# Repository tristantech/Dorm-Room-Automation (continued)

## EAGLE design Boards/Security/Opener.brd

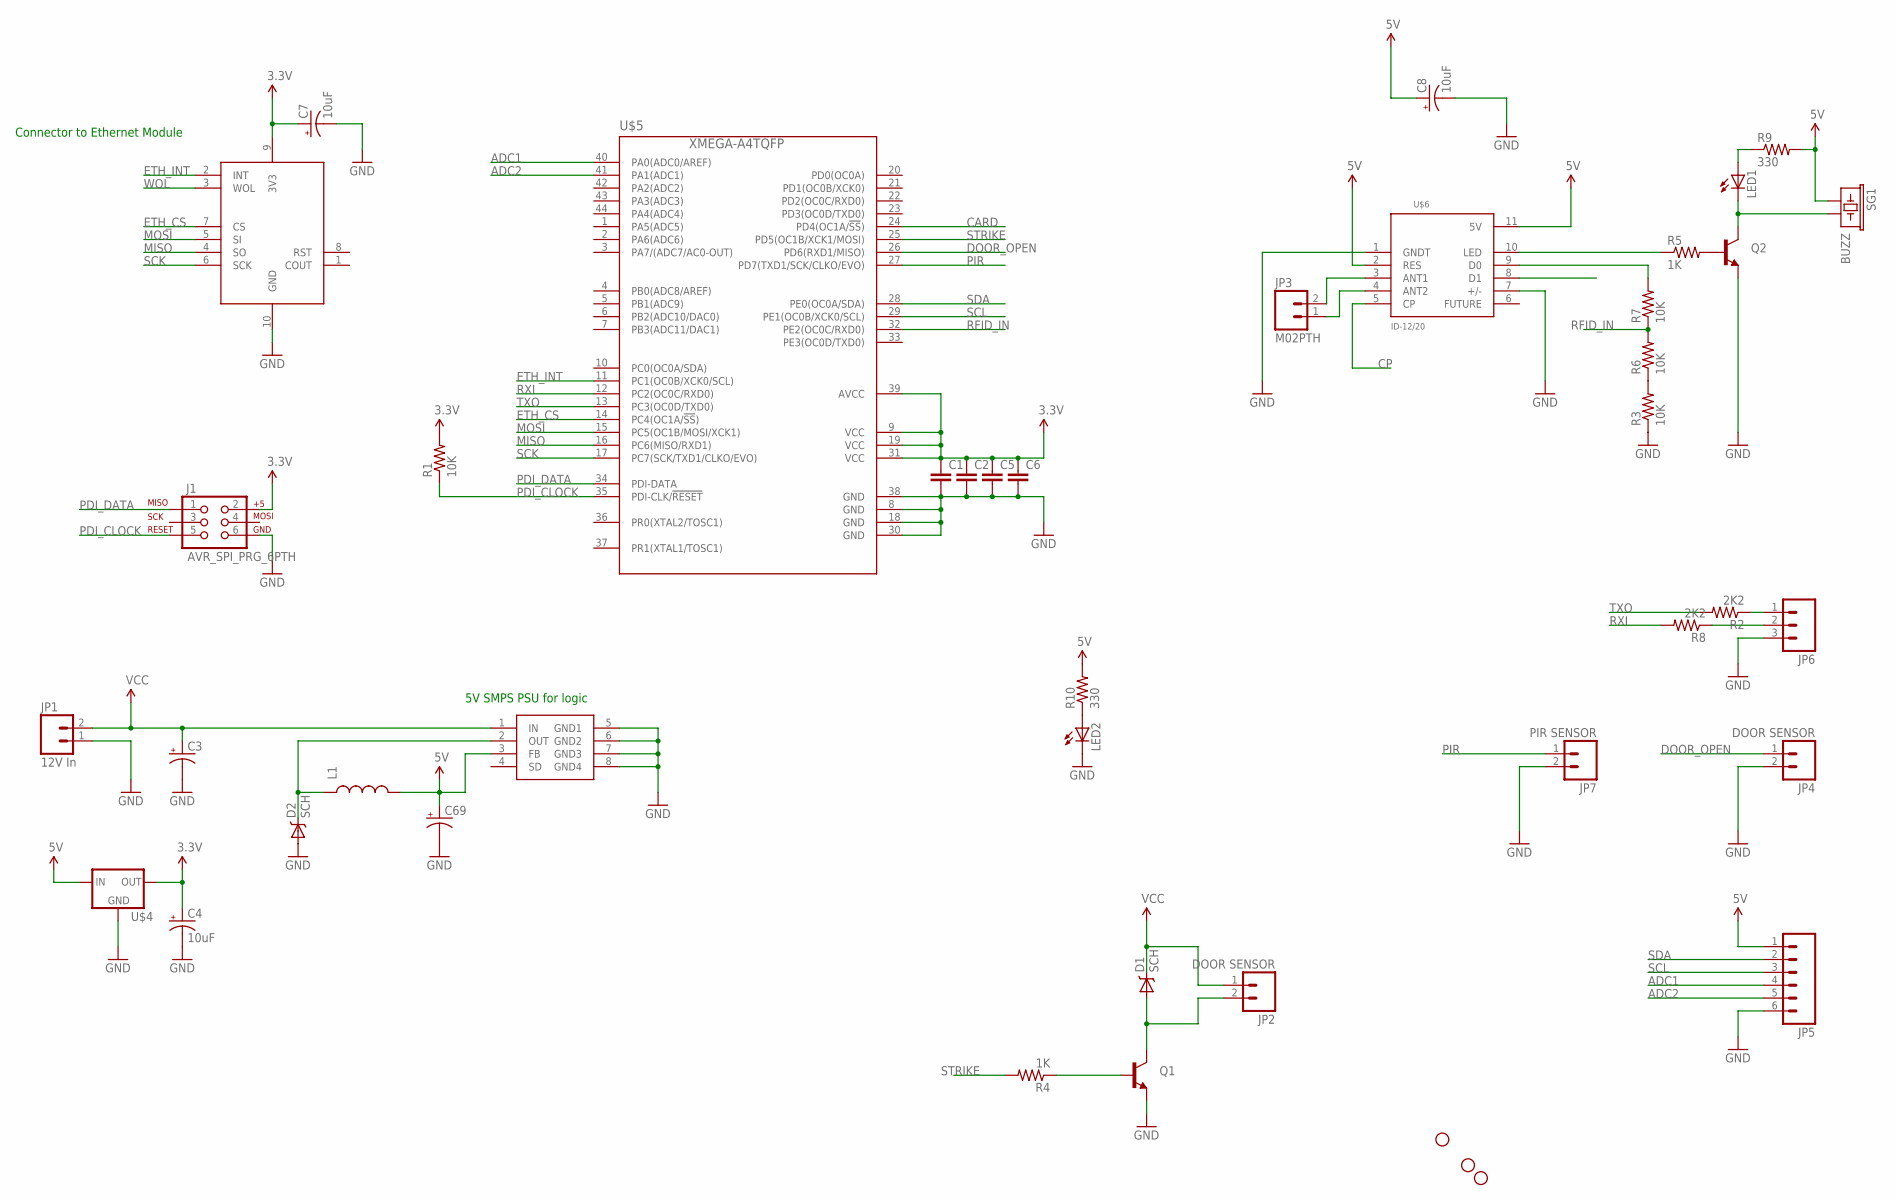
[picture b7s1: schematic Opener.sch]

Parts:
C1, C2, C5, C6: CAP0603-CAP; 0603-CAP
C3, C69: CAP_POLPTH1; CPOL-RADIAL-100UF-25V
C4, C7, C8: 10uF; EIA3216
D1, D2: SCH; SMA-DIODE
J1: AVR_SPI_PRG_6PTH; 2X3
JP1: 12V In; SCREWTERMINAL-3.5MM-2
JP2, JP4: DOOR SENSOR; MOLEX-1X2
JP3: M02PTH; 1X02
JP5: M06SIP; 1X06
JP6: M03PTH; 1X03
JP7: PIR SENSOR; MOLEX-1X2
L1: INDUCTOR1206H*; INDUCTOR-1206
LED1, LED2: LED-FKIT-1206; FKIT-LED-1206
Q1: TRANSISTOR_NPNTO92; TO-92
Q2: TRANSISTOR_NPNSOT23; SOT23
R1, R3, R6, R7: 10K; 1206
R2, R8: 2K2; 1206
R4, R5: 1K; 1206
R9, R10: 330; 1206
SG1: BUZZ; BUZZER-CCV
STANDOFF1, STANDOFF3, STANDOFF4: STAND-OFF
U$1: ETHMODULE; 2X5
U$3: AP1509-33; SOIC-8
U$4: V_REG_MIC2920; SOT223
U$5: XMEGA-A4TQFP; TQFP44
U$6: ID-12/20; ID-12

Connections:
3.3V: C1.1, C2.1, C4.A (+), C5.1, C6.1, C7.A (+), J1.2, R1.2, U$1.9 (3V3), U$4.3 (OUT), U$5.9 (VCC), U$5.19 (VCC), U$5.31 (VCC), U$5.39 (AVCC)
5V: C8.A (+), C69.1 (+), JP5.1, L1.P$2 (2), R9.2, R10.2, SG1.+ (1), U$3.3 (FB), U$4.1 (IN), U$6.2 (RES), U$6.11 (5V)
ADC1: JP5.4, U$5.40 (PA0(ADC0/AREF))
ADC2: JP5.5, U$5.41 (PA1(ADC1))
CARD: U$5.24 (PD4(OC1A/!SS!))
COUT: U$1.1 (COUT)
CP: U$6.5 (CP)
DOOR_OPEN: JP4.1, U$5.26 (PD6(RXD1/MISO))
ETH_CS: U$1.7 (CS), U$5.14 (PC4(OC1A/!SS!))
ETH_INT: U$1.2 (INT), U$5.11 (PC1(OC0B/XCK0/SCL))
GND: C1.2, C2.2, C3.2 (-), C4.C (-), C5.2, C6.2, C7.C (-), C8.C (-), C69.2 (-), D2.A, J1.6, JP1.1, JP4.2, JP5.6, JP6.3, JP7.2, LED2.C, Q1.1 (E), Q2.2 (E), R3.1, U$1.10 (GND), U$3.5 (GND1), U$3.6 (GND2), U$3.7 (GND3), U$3.8 (GND4), U$4.2 (GND), U$5.8 (GND), U$5.18 (GND), U$5.30 (GND), U$5.38 (GND), U$6.1 (GNDT), U$6.7 (+/-)
MISO: U$1.4 (SO), U$5.16 (PC6(MISO/RXD1))
MOSI: U$1.5 (SI), U$5.15 (PC5(OC1B/MOSI/XCK1))
unnamed: Q1.2 (B), R4.1
unnamed: JP3.2, U$6.3 (ANT1)
unnamed: D2.C, L1.P$1 (1), U$3.2 (OUT)
unnamed: R7.2, U$6.9 (D0)
unnamed: R3.2, R6.1
unnamed: JP3.1, U$6.4 (ANT2)
unnamed: D1.A, JP2.2, Q1.3 (C)
unnamed: R5.1, U$6.10 (LED)
unnamed: Q2.1 (B), R5.2
unnamed: LED1.C, Q2.3 (C), SG1.- (2)
unnamed: LED1.A, R9.1
unnamed: JP6.1, R2.1
unnamed: LED2.A, R10.1
unnamed: JP6.2, R8.1
PDI_CLOCK: J1.5, R1.1, U$5.35 (PDI-CLK/!RESET)
PDI_DATA: J1.1, U$5.34 (PDI-DATA)
PIR: JP7.1, U$5.27 (PD7(TXD1/SCK/CLKO/EVO))
RFID_IN: R6.2, R7.1, U$5.32 (PE2(OC0C/RXD0))
RST: U$1.8 (RST)
RXI: R8.2, U$5.12 (PC2(OC0C/RXD0))
SCK: U$1.6 (SCK), U$5.17 (PC7(SCK/TXD1/CLKO/EVO))
SCL: JP5.3, U$5.29 (PE1(OC0B/XCK0/SCL))
SDA: JP5.2, U$5.28 (PE0(OC0A/SDA))
STRIKE: R4.2, U$5.25 (PD5(OC1B/XCK1/MOSI))
TXO: R2.2, U$5.13 (PC3(OC0D/TXD0))
VCC: C3.1 (+), D1.C, JP1.2, JP2.1, U$3.1 (IN)
WOL: U$1.3 (WOL)

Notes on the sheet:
Connector to Ethernet Module
5V SMPS PSU for logic

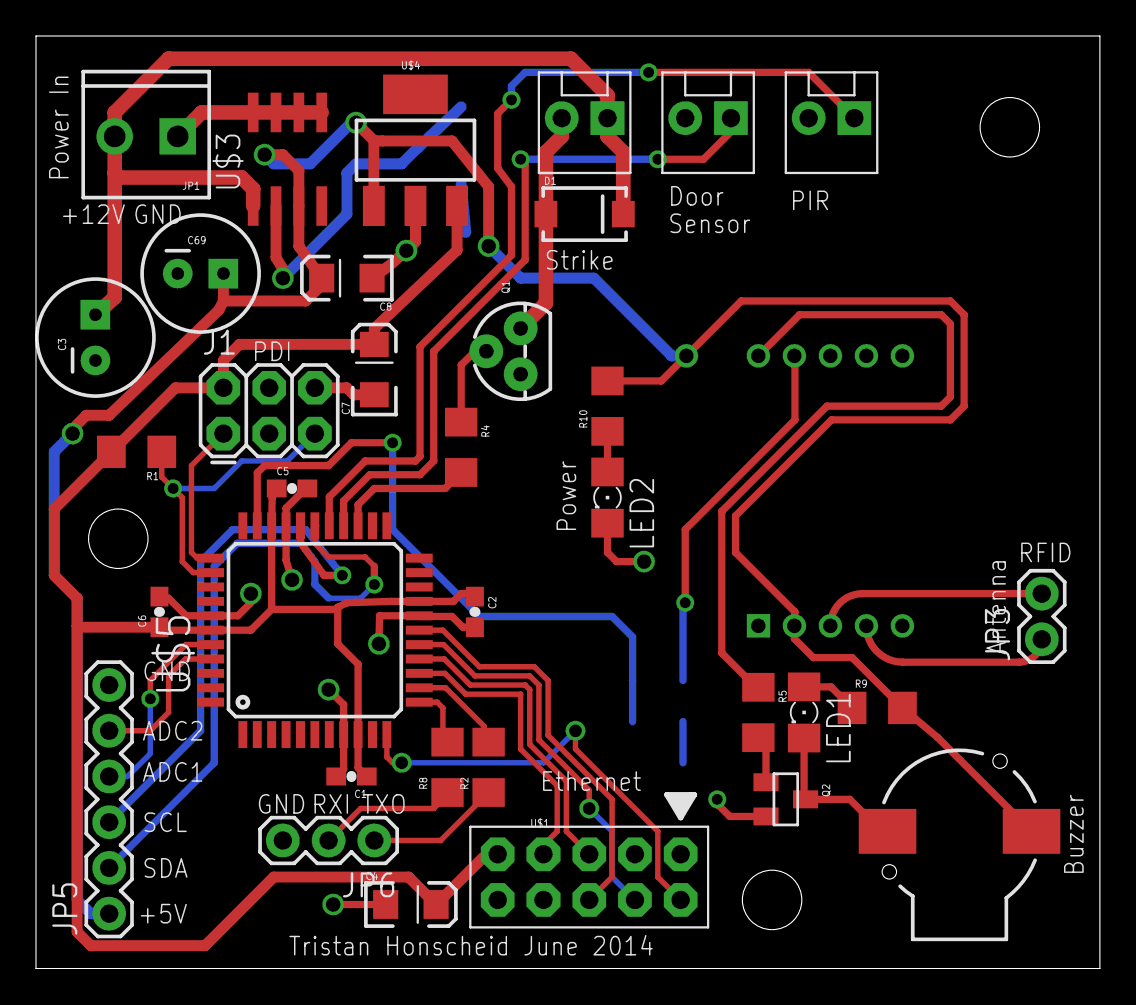
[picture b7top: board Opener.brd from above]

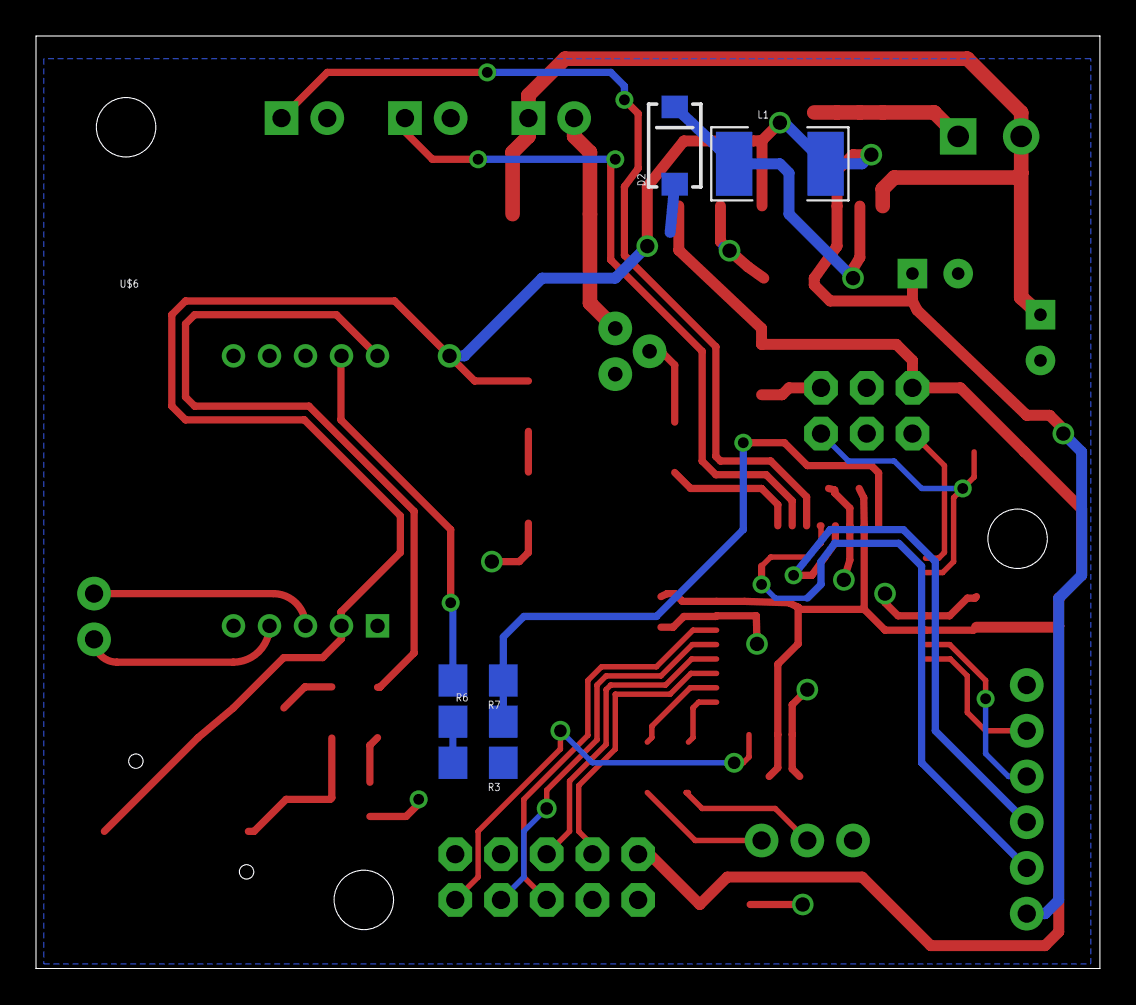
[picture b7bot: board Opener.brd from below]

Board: 2 copper layers, 59.1 x 51.8 mm, 43 parts (6 on the bottom side), 35 nets.

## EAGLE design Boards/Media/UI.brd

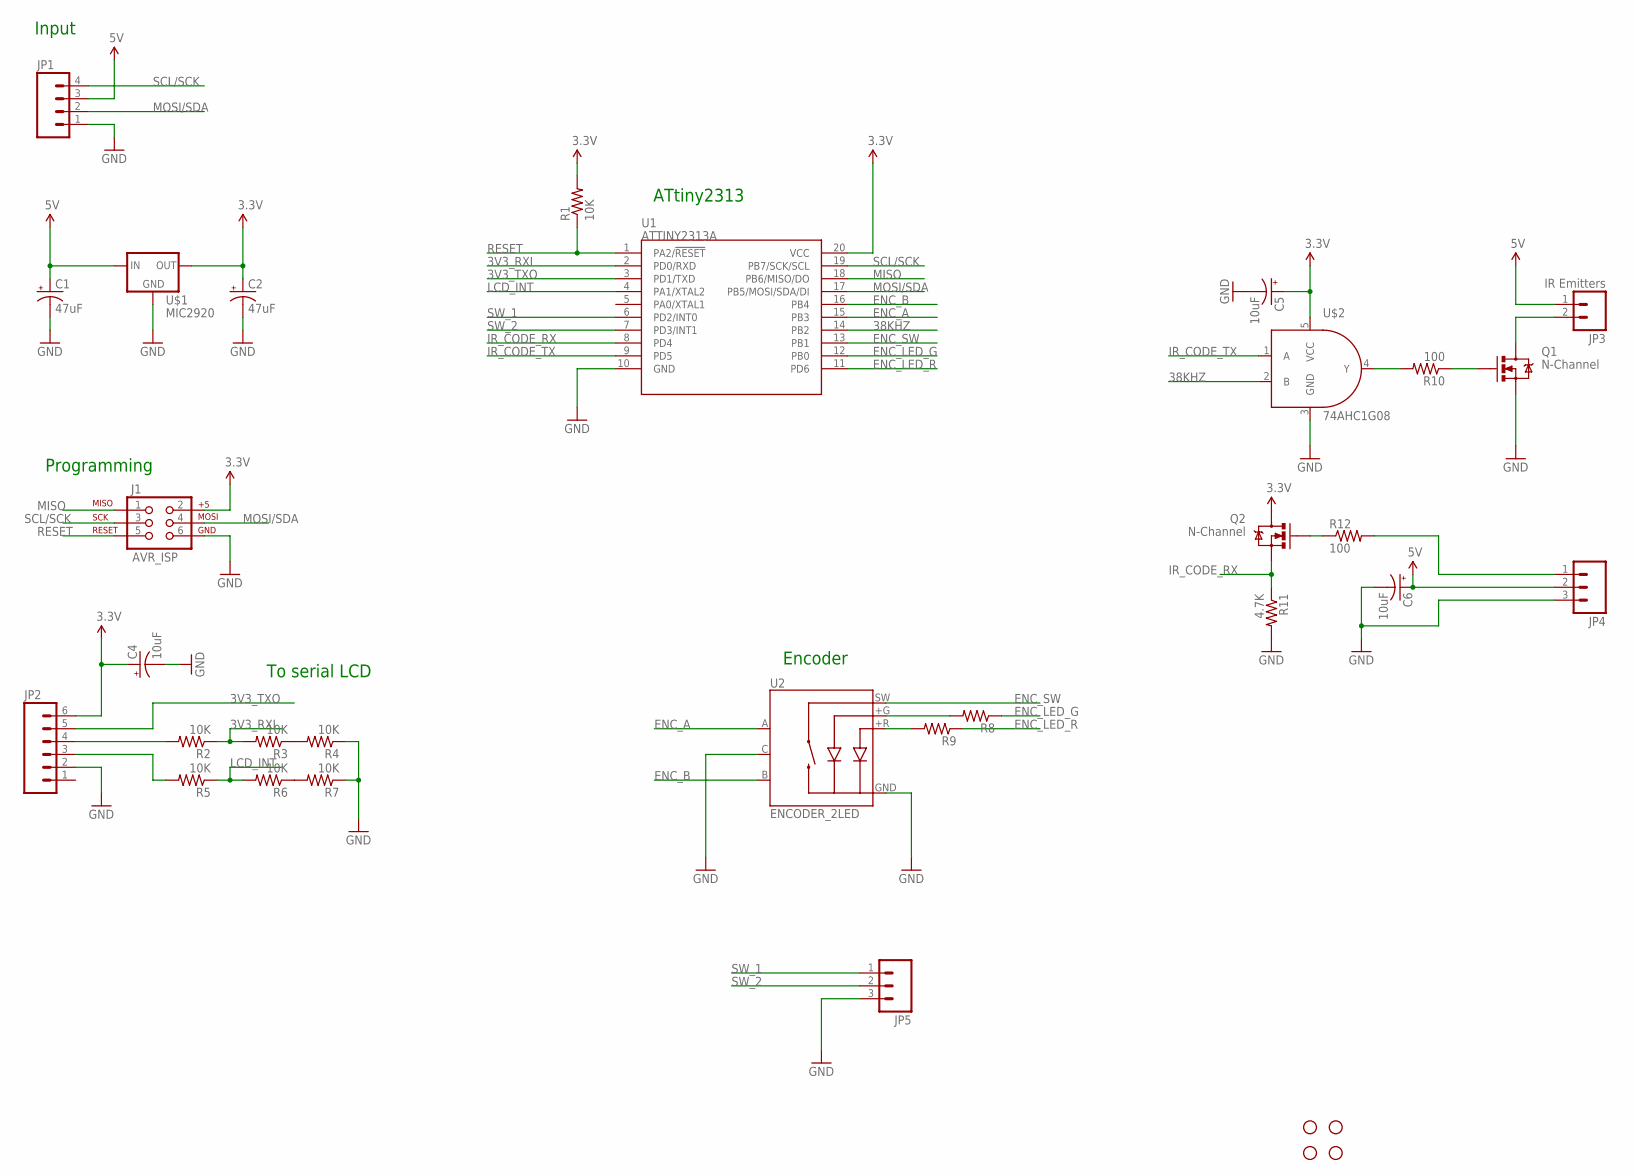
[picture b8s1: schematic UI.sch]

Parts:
C1, C2: 47uF; CPOL-RADIAL-10UF-25V
C4, C5, C6: 10uF; EIA3216
J1: AVR_ISP; 2X3
JP1: M04POLAR; MOLEX-1X4
JP2: M06POLAR; MOLEX-1X6
JP3: IR Emitters; SCREWTERMINAL-3.5MM-2
JP4, JP5: M03PTH; 1X03
Q1, Q2: N-Channel; SOT23
R1, R2, R3, R4, R5, R6, R7: 10K; 1206
R8, R9: RESISTOR1206; 1206
R10, R12: 100; 1206
R11: 4.7K; 1206
STANDOFF1, STANDOFF2, STANDOFF3, STANDOFF4: STAND-OFF
U1: ATTINY2313A; SOP20W
U2: ENCODER_2LED; ENCODER_LED_2
U$1: MIC2920; SOT223
U$2: 74AHC1G08; SOT23-5

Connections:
3.3V: C2.1 (+), C4.A (+), C5.A (+), J1.2, JP2.6, Q2.3 (D), R1.2, U1.20 (VCC), U$1.3 (OUT), U$2.5 (VCC)
3V3_RXI: R2.1, R3.2, U1.2 (PD0/RXD)
3V3_TXO: JP2.5, U1.3 (PD1/TXD)
5V: C1.1 (+), C6.A (+), JP1.3, JP3.1, JP4.2, U$1.1 (IN)
38KHZ: U1.14 (PB2), U$2.2 (B)
ENC_A: U1.15 (PB3), U2.A
ENC_B: U1.16 (PB4), U2.B
ENC_LED_G: R8.1, U1.12 (PB0)
ENC_LED_R: R9.1, U1.11 (PD6)
ENC_SW: U1.13 (PB1), U2.SW
GND: C1.2 (-), C2.2 (-), C4.C (-), C5.C (-), C6.C (-), J1.6, JP1.1, JP2.2, JP4.3, JP5.3, Q1.2 (S), R4.1, R7.1, R11.2, U1.10 (GND), U2.C, U2.GND (-), U$1.2 (GND), U$2.3 (GND)
IR_CODE_RX: Q2.2 (S), R11.1, U1.8 (PD4)
IR_CODE_TX: U1.9 (PD5), U$2.1 (A)
LCD_INT: R5.1, R6.2, U1.4 (PA1/XTAL2)
MISO: J1.1, U1.18 (PB6/MISO/DO)
MOSI/SDA: J1.4, JP1.2, U1.17 (PB5/MOSI/SDA/DI)
unnamed: R8.2, U2.+G
unnamed: R9.2, U2.+R
unnamed: JP4.1, R12.2
unnamed: JP2.4, R2.2
unnamed: JP2.3, R5.2
unnamed: R3.1, R4.2
unnamed: R6.1, R7.2
unnamed: JP3.2, Q1.3 (D)
unnamed: R10.2, U$2.4 (Y)
unnamed: Q1.1 (G), R10.1
unnamed: Q2.1 (G), R12.1
RESET: J1.5, R1.1, U1.1 (PA2/!RESET)
SCL/SCK: J1.3, JP1.4, U1.19 (PB7/SCK/SCL)
SW_1: JP5.1, U1.6 (PD2/INT0)
SW_2: JP5.2, U1.7 (PD3/INT1)

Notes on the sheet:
To serial LCD
Programming
Input
ATtiny2313
Encoder

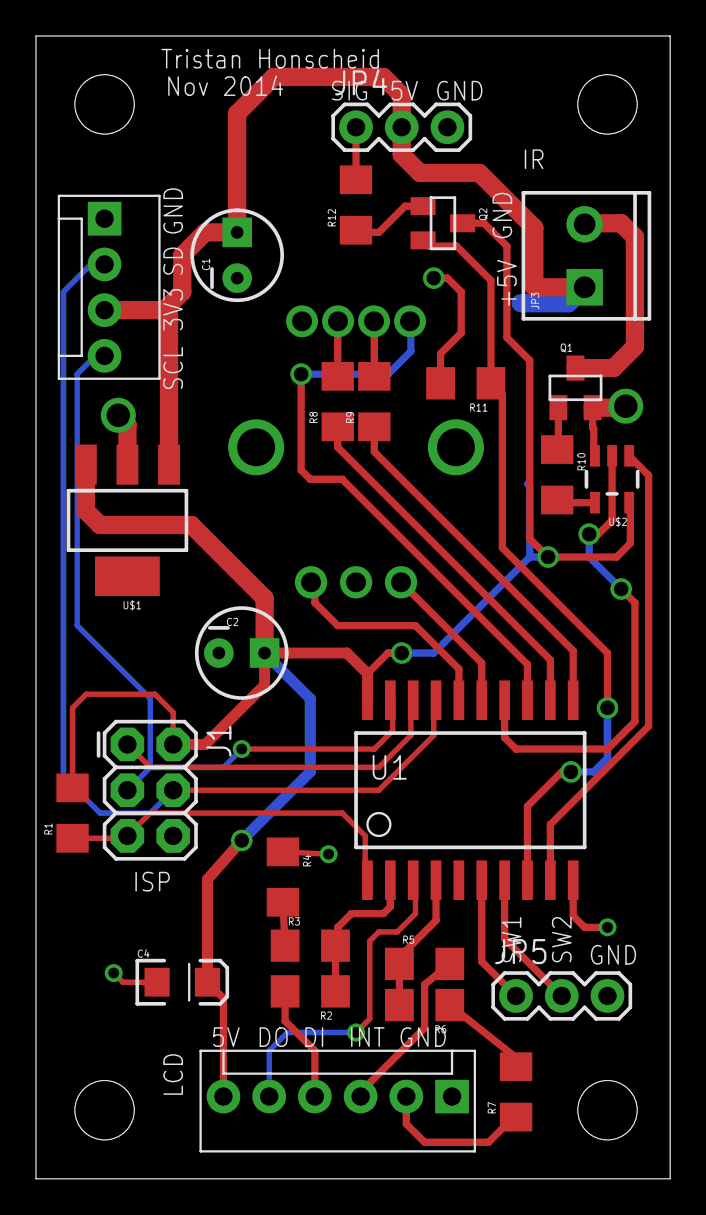
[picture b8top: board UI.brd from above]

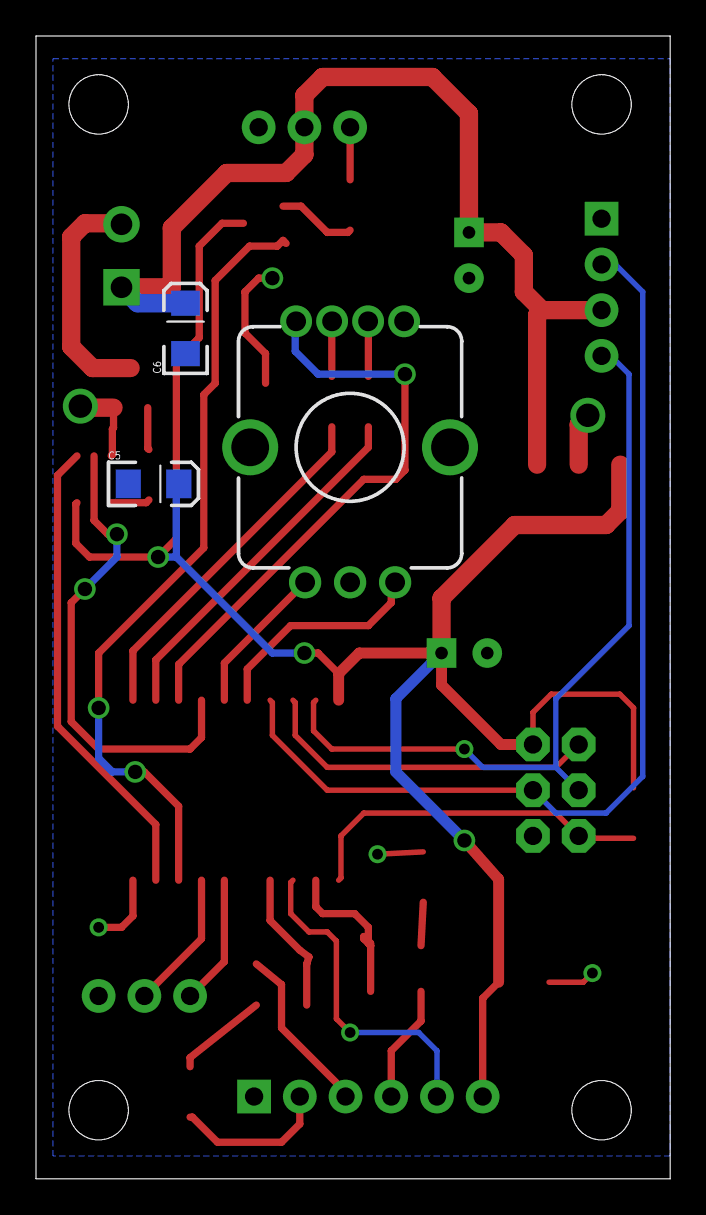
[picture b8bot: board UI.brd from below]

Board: 2 copper layers, 35.2 x 63.5 mm, 33 parts (3 on the bottom side), 31 nets.

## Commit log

2014-10-31 First commit of existing code to Github
2014-11-01 Finished PWM lighting board, now uses a ribbon cable to connect to a break out terminal board
2014-11-01 Added small breakout board for the STA540 amplifier
2014-11-26 Lots of prgress on media related boards.
2014-11-27 Changed to a PI GPIO header (ditching the NGW100)
2014-12-01 DSP sch nearly complete, added most components. Still needs reset generator and final check
2014-12-03 Began laying out DSP board
2014-12-10 DSP Board finished!
2014-12-10 Prepared board for production, last minute error checks and rotations
2014-12-12 Final gerbers and board updates! Fixed PCB violations, now passes FreeDFM check!
